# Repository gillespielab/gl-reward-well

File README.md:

# gl-reward-well
The PCB design for the reward wells

To manufacture new boards, download all the files, zip them, and then upload that to the PCB manufacturer of your choice.

original design by Demetris Roumis: https://figshare.com/articles/software/physiology/4747438?file=7784095

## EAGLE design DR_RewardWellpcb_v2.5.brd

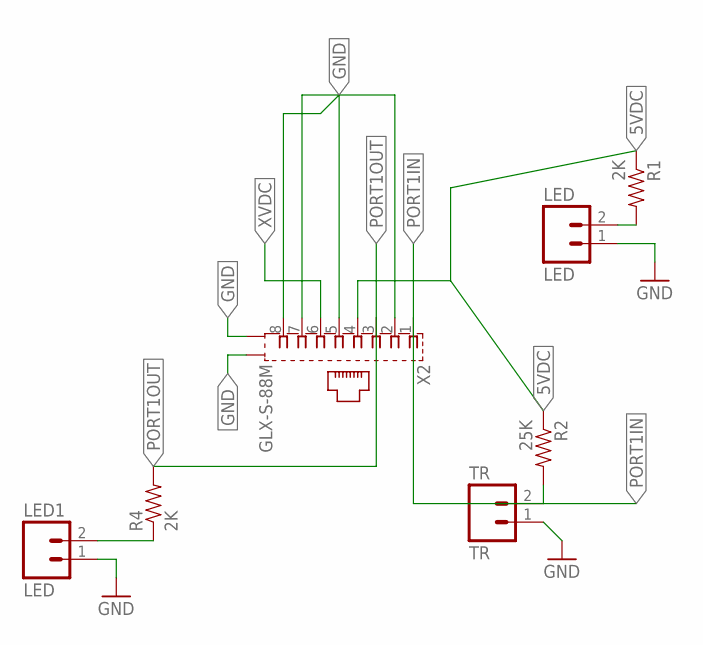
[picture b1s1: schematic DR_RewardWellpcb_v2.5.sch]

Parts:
LED, LED1: LED; 1X02
R1, R4: 2K; 1206
R2: 25K; 1206
TR: TR; 1X02
X2: GLX-S-88M

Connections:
5VDC: R1.1, R2.1, X2.4
GND: LED.1, LED1.1, TR.1, X2.2, X2.7, X2.8, X2.S1, X2.S2
unnamed: LED.2, R1.2
unnamed: LED1.2, R4.1
PORT1IN: R2.2, TR.2, X2.1
PORT1OUT: R4.2, X2.3
XVDC: X2.6

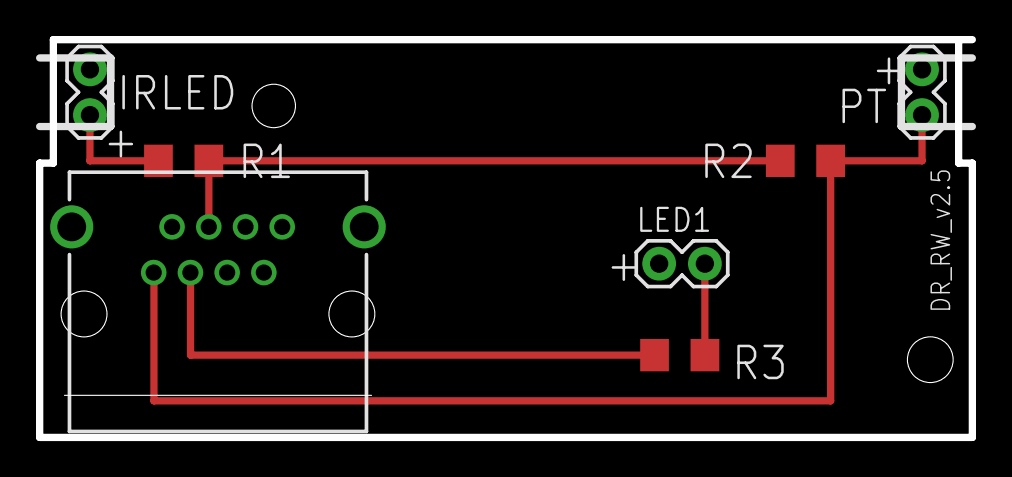
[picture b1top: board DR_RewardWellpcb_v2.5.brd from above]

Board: 2 copper layers, 51.8 x 22.1 mm, 7 parts (1 on the bottom side), 6 nets.
